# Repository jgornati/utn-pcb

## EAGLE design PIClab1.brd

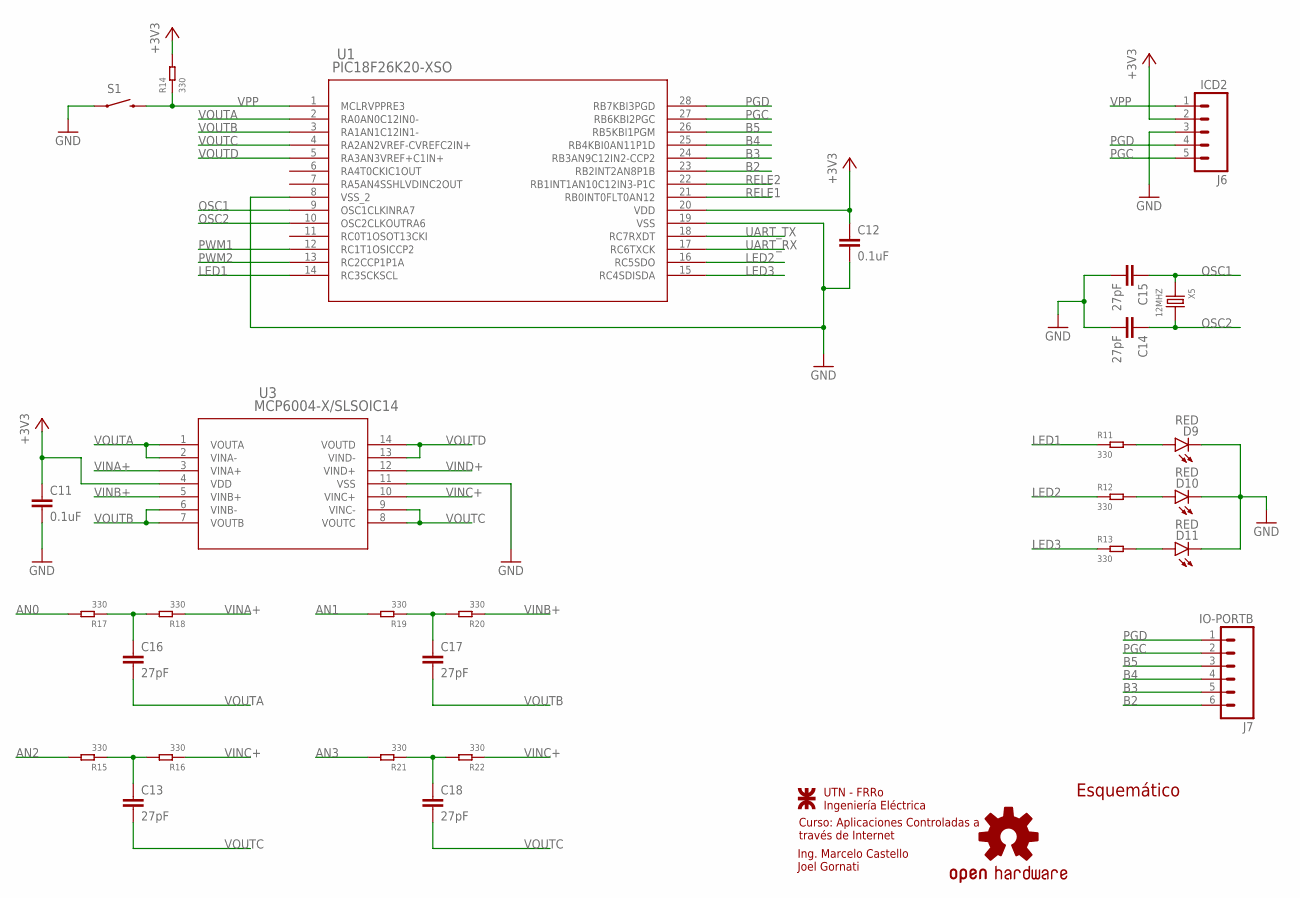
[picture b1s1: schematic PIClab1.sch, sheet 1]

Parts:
C11, C12: 0.1uF; 1206
C13, C14, C15, C16, C17, C18: 27pF; 1206
D9, D10, D11: RED; LED-1206
J6: ICD2; 1X05
J7: IO-PORTB; 1X06
LOGO2: OSHW-LOGOMINI; OSHW-LOGO-MINI
R11, R12, R13, R14, R15, R16, R17, R18, R19, R20, R21, R22: 330; R1206
S1: SWITCH-MOMENTARY-2SMD-4; TACTILE_SWITCH_TALL
U1: PIC18F26K20-XSO; SOIC28-W_MC
U3: MCP6004-X/SLSOIC14; SOIC14-N_MC
U$3: UTNLOGO
X5: 12MHZ; HC49UP

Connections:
+3V3: C11.1, C12.1, J6.2, R14.2, U1.20 (VDD), U3.4 (VDD); also elsewhere on the board
AN0: R17.2
AN1: R19.2
AN2: R15.2
AN3: R21.2
B2: J7.6, U1.23 (RB2INT2AN8P1B)
B3: J7.5, U1.24 (RB3AN9C12IN2-CCP2)
B4: J7.4, U1.25 (RB4KBI0AN11P1D)
B5: J7.3, U1.26 (RB5KBI1PGM)
GND: C11.2, C12.2, C14.2, C15.2, D9.C, D10.C, D11.C, J6.3, S1.A2 (1), U1.8 (VSS_2), U1.19 (VSS), U3.11 (VSS); also elsewhere on the board
LED1: R11.1, U1.14 (RC3SCKSCL)
LED2: R12.1, U1.16 (RC5SDO)
LED3: R13.1, U1.15 (RC4SDISDA)
unnamed: C13.1, R15.1, R16.2
unnamed: C17.1, R19.1, R20.2
unnamed: C18.1, R21.1, R22.2
unnamed: D9.A, R11.2
unnamed: D10.A, R12.2
unnamed: D11.A, R13.2
unnamed: C16.1, R17.1, R18.2
OSC1: C15.1, U1.9 (OSC1CLKINRA7), X5.1
OSC2: C14.1, U1.10 (OSC2CLKOUTRA6), X5.2
PGC: J6.5, J7.2, U1.27 (RB6KBI2PGC)
PGD: J6.4, J7.1, U1.28 (RB7KBI3PGD)
PWM1: U1.12 (RC1T1OSICCP2)
PWM2: U1.13 (RC2CCP1P1A)
RELE1: U1.21 (RB0INT0FLT0AN12); also elsewhere on the board
RELE2: U1.22 (RB1INT1AN10C12IN3-P1C); also elsewhere on the board
UART_RX: U1.17 (RC6TXCK); also elsewhere on the board
UART_TX: U1.18 (RC7RXDT); also elsewhere on the board
VINA+: R18.1, U3.3 (VINA+)
VINB+: R20.1, U3.5 (VINB+)
VINC+: R16.1, R22.1, U3.10 (VINC+)
VIND+: U3.12 (VIND+)
VOUTA: C16.2, U1.2 (RA0AN0C12IN0-), U3.1 (VOUTA), U3.2 (VINA-)
VOUTB: C17.2, U1.3 (RA1AN1C12IN1-), U3.6 (VINB-), U3.7 (VOUTB)
VOUTC: C13.2, C18.2, U1.4 (RA2AN2VREF-CVREFC2IN+), U3.8 (VOUTC), U3.9 (VINC-)
VOUTD: U1.5 (RA3AN3VREF+C1IN+), U3.13 (VIND-), U3.14 (VOUTD)
VPP: J6.1, R14.1, S1.B2 (2), U1.1 (MCLRVPPRE3)

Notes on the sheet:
Esquemático
UTN - FRRo
Ingeniería Eléctrica
Ing. Marcelo Castello Joel Gornati
Curso: Aplicaciones Controladas a través de Internet

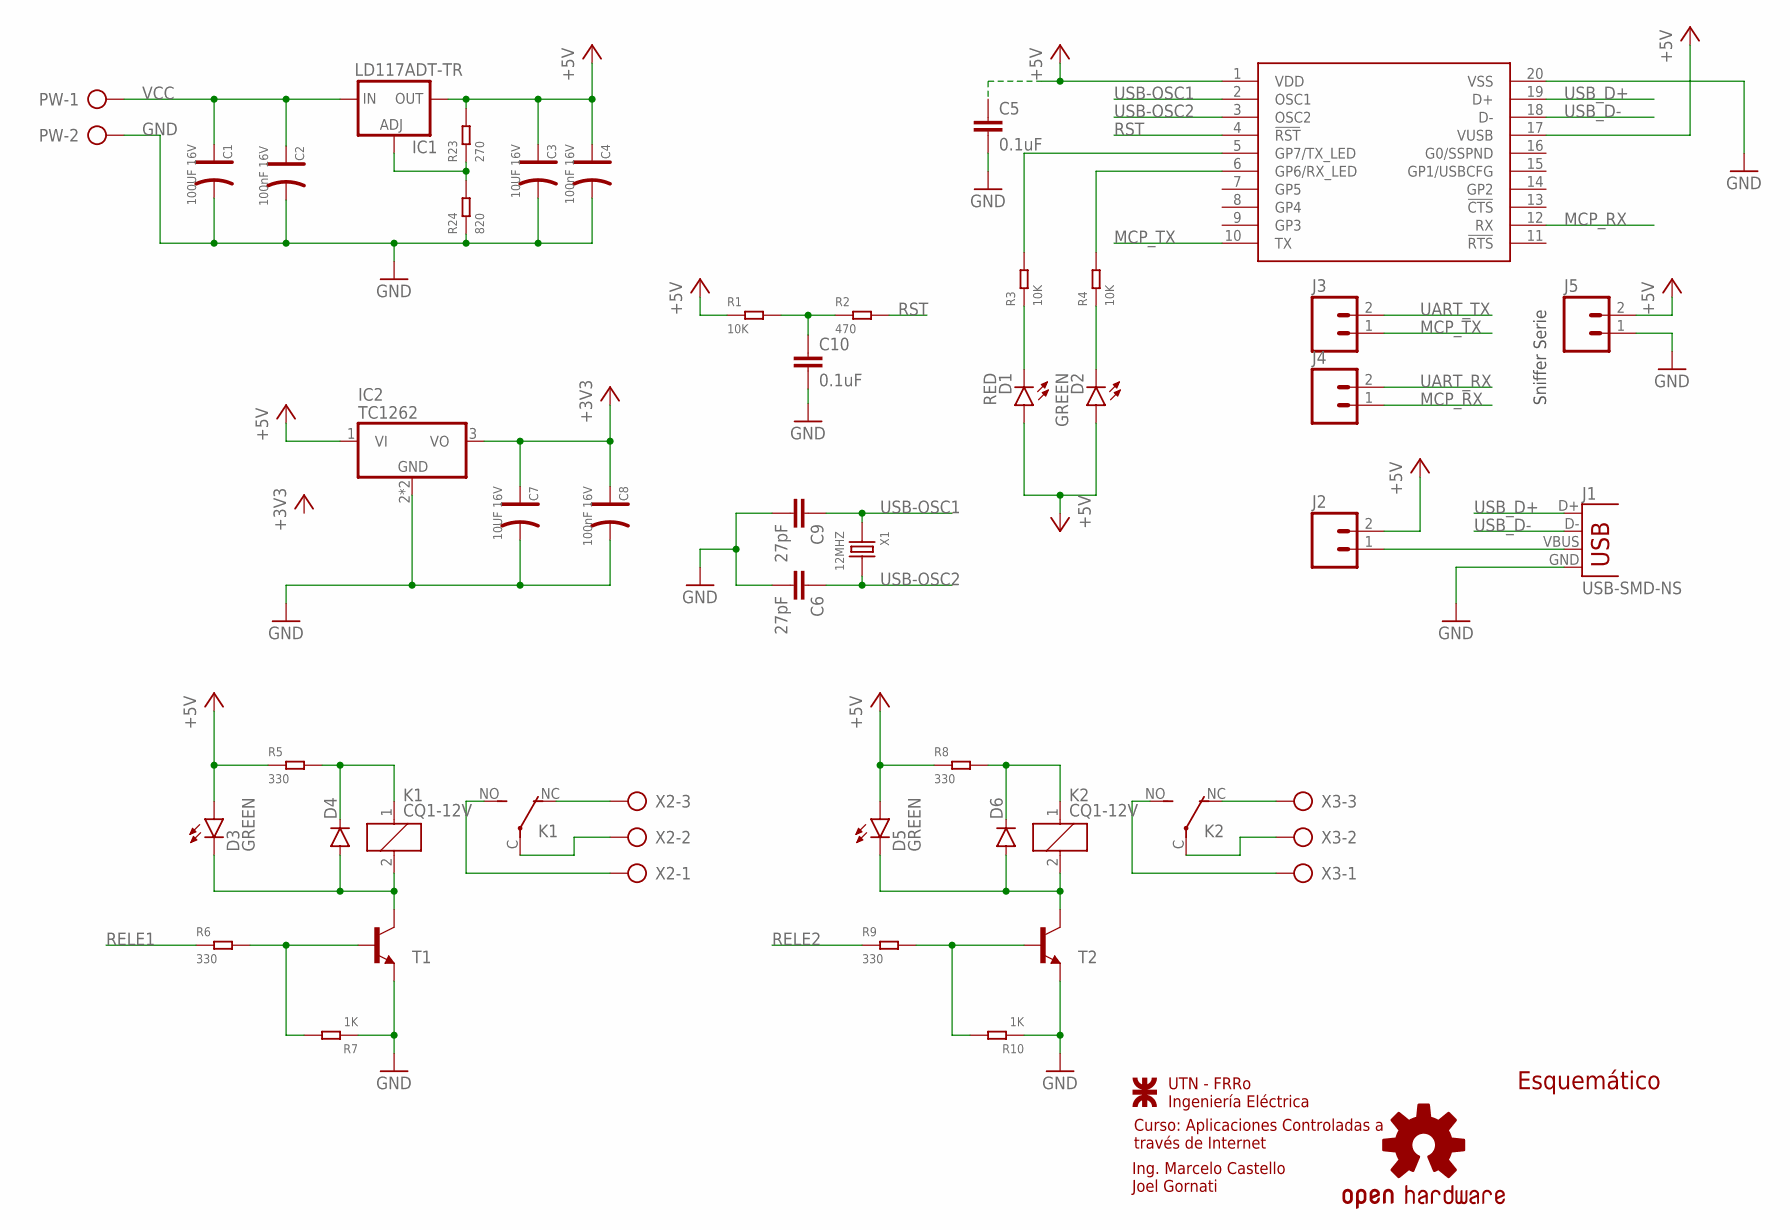
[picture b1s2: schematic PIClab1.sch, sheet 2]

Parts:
C1: 100UF 16V; ELECTRO-SMD-A-3.8MM
C2, C4, C8: 100nF 16V; ELECTRO-SMD-A-3.8MM
C3, C7: 10UF 16V; ELECTRO-SMD-A-3.8MM
C5, C10: 0.1uF; 1206
C6, C9: 27pF; 1206
D1: RED; LED-1206
D2, D3, D5: GREEN; LED-1206
D4, D6: DIODEHV; DIODE-HV
IC1: LD117ADT-TR; DPACK
IC2: TC1262; SOT223
J1: USB-SMD-NS; USB-MINIB-NOSTOP
J2, J3, J4, J5: M02PTH; 1X02
K1, K2: CQ1-12V; CQ1
LOGO1: OSHW-LOGOMINI; OSHW-LOGO-MINI
PW: AK300/2
R1, R3, R4: 10K; R1206
R2: 470; R1206
R5, R6, R8, R9: 330; R1206
R7, R10: 1K; R1206
R23: 270; R1206
R24: 820; R1206
T1, T2: BC817-25-NPN-SOT23-BEC; SOT23-BEC
U2: MCP2200SOIC; MCP2200
U$2: UTNLOGO
X1: 12MHZ; HC49UP
X2, X3: AK500/3

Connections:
+3V3: C7.+, C8.+, IC2.3 (VO); also elsewhere on the board
+5V: C3.+, C4.+, C5.1, D1.A, D2.A, D3.A, D5.A, IC1.4 (OUT), IC2.1 (VI), J2.2, J5.2, R1.1, R5.1, R8.1, R23.2, U2.1 (VDD), U2.17 (VUSB)
GND: C1.-, C2.-, C3.-, C4.-, C5.2, C6.2, C7.-, C8.-, C9.2, C10.2, IC2.2 (GND), IC2.4 (GND), J1.GND, J5.1, PW.2, R7.1, R10.1, R24.1, T1.E, T2.E, U2.20 (VSS); also elsewhere on the board
MCP_RX: J4.1, U2.12 (RX)
MCP_TX: J3.1, U2.10 (TX)
unnamed: C10.1, R1.2, R2.1
unnamed: K1.C, X2.2
unnamed: D2.C, R4.1
unnamed: D1.C, R3.1
unnamed: R3.2, U2.5 (GP7/TX_LED)
unnamed: R4.2, U2.6 (GP6/RX_LED)
unnamed: K1.NC (O), X2.3
unnamed: K1.NO (S), X2.1
unnamed: J1.VBUS, J2.1
unnamed: D3.C, D4.A, K1.2, T1.C
unnamed: D4.C, K1.1, R5.2
unnamed: R6.2, R7.2, T1.B
unnamed: K2.C, X3.2
unnamed: K2.NC (O), X3.3
unnamed: K2.NO (S), X3.1
unnamed: D5.C, D6.A, K2.2, T2.C
unnamed: D6.C, K2.1, R8.2
unnamed: R9.2, R10.2, T2.B
unnamed: IC1.1 (ADJ), R23.1, R24.2
RELE1: R6.1; also elsewhere on the board
RELE2: R9.1; also elsewhere on the board
RST: R2.2, U2.4 (!RST)
UART_RX: J4.2; also elsewhere on the board
UART_TX: J3.2; also elsewhere on the board
USB-OSC1: C9.1, U2.2 (OSC1), X1.1
USB-OSC2: C6.1, U2.3 (OSC2), X1.2
USB_D+: J1.D+, U2.19 (D+)
USB_D-: J1.D-, U2.18 (D-)
VCC: C1.+, C2.+, IC1.3 (IN), PW.1

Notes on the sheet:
Esquemático
UTN - FRRo
Ingeniería Eléctrica
Ing. Marcelo Castello Joel Gornati
Curso: Aplicaciones Controladas a través de Internet
Sniffer Serie

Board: 2 copper layers, 77 parts (0 on the bottom side), 60 nets, no tracks yet.

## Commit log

2016-07-15 kick

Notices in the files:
parts and their libraries:
SparkFun-Passives: Licensing: Creative Commons ShareAlike 4.0 International - https://creativecommons.org/licenses/by-sa/4.0
